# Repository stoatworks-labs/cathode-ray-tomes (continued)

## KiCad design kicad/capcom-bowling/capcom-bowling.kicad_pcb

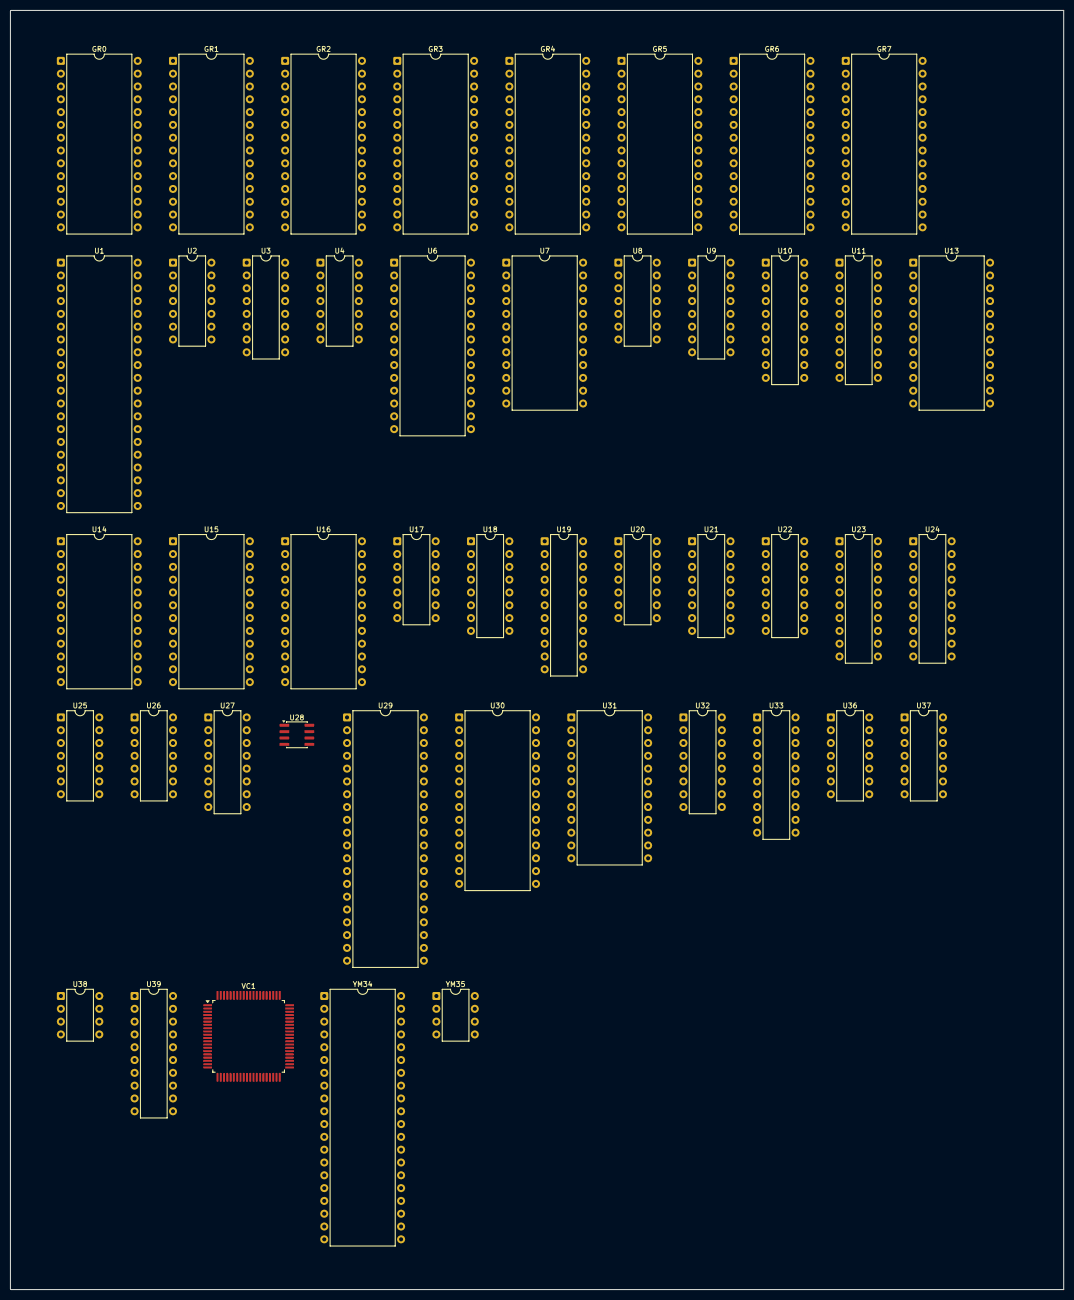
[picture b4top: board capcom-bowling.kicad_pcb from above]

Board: 2 copper layers, 208.9 x 253.7 mm, 46 parts (0 on the bottom side), 174 nets, no tracks yet.

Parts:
GR0, GR1, GR2, GR3, GR4, GR5, GR6, GR7: 27C256; DIP-28_W15.24mm
U1, U29: MC68B09E; DIP-40_W15.24mm
U2, U25: 74LS74; DIP-14_W7.62mm
U3: 74LS76; DIP-16_W7.62mm
U4: 74LS10; DIP-14_W7.62mm
U6, U30: 27C256; DIP-28_W15.24mm
U7, U31: HM6116P-3; DIP-24_W15.24mm
U8: 74LS04; DIP-14_W7.62mm
U9, U18, U32: 74LS138; DIP-16_W7.62mm
U10, U11, U33: 74HCT374; DIP-20_W7.62mm
U13, U14, U15, U16: TMS4461-15NL; DIP-24_W15.24mm
U17: 74LS14; DIP-14_W7.62mm
U19: TMS34070NL; DIP-22_W7.62mm
U20: 74LS86; DIP-14_W7.62mm
U21, U22, U27: 74LS191; DIP-16_W7.62mm
U23, U24: 74LS244; DIP-20_W7.62mm
U26: 74LS32; DIP-14_W7.62mm
U28: NE555; SOIC-8_3.9x4.9mm_P1.27mm
U36, U37: MC3403N; DIP-14_W7.62mm
U38: MB3730; DIP-8_W7.62mm
U39: DAC0832LCN; DIP-20_W7.62mm
VC1: TMS34061FNL; PQFP-80_14x14mm_P0.65mm
YM34: YM2203; DIP-40_W15.24mm
YM35: YM3014; DIP-8_W7.62mm

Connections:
/1P_START: U17.5, U24.15
/ PAL_MODE: U4.10, U4.11, U11.19
/-5V: U37.11, U39.8
/A0: GR0.10, GR1.10, GR2.10, GR3.10, GR4.10, GR5.10, GR6.10, GR7.10, U1.8, U6.10, U7.8, VC1.54
/A1: GR0.9, GR1.9, GR2.9, GR3.9, GR4.9, GR5.9, GR6.9, GR7.9, U1.9, U6.9, U7.7, U8.5
/A2: GR0.8, GR1.8, GR2.8, GR3.8, GR4.8, GR5.8, GR6.8, GR7.8, U1.10, U6.8, U7.6, VC1.51
/A3: GR0.7, GR1.7, GR2.7, GR3.7, GR4.7, GR5.7, GR6.7, GR7.7, U1.11, U6.7, U7.5, VC1.50
/A4: GR0.6, GR1.6, GR2.6, GR3.6, GR4.6, GR5.6, GR6.6, GR7.6, U1.12, U6.6, U7.4, VC1.49
/A5: GR0.5, GR1.5, GR2.5, GR3.5, GR4.5, GR5.5, GR6.5, GR7.5, U1.13, U6.5, U7.3, VC1.48
/A6: GR0.4, GR1.4, GR2.4, GR3.4, GR4.4, GR5.4, GR6.4, GR7.4, U1.14, U6.4, U7.2, VC1.47
/A7: GR0.3, GR1.3, GR2.3, GR3.3, GR4.3, GR5.3, GR6.3, GR7.3, U1.15, U6.3, U7.1, VC1.46
/A8: GR0.25, GR1.25, GR2.25, GR3.25, GR4.25, GR5.25, GR6.25, GR7.25, U1.16, U6.25, U7.23, U26.13, VC1.32
/A9: GR0.24, GR1.24, GR2.24, GR3.24, GR4.24, GR5.24, GR6.24, GR7.24, U1.17, U6.24, U7.22, U26.12, VC1.33
/A10: GR0.21, GR1.21, GR2.21, GR3.21, GR4.21, GR5.21, GR6.21, GR7.21, U1.18, U6.21, U7.19
/A11: GR0.23, GR1.23, GR2.23, GR3.23, GR4.23, GR5.23, GR6.23, GR7.23, U1.19, U6.23, U9.1
/A12: GR0.2, GR1.2, GR2.2, GR3.2, GR4.2, GR5.2, GR6.2, GR7.2, U1.20, U6.2
/A13: GR0.26, GR1.26, GR2.26, GR3.26, GR4.26, GR5.26, GR6.26, GR7.26, U1.21, U6.26, U9.2
/A14: U1.22, U6.27, U9.6, U18.5
/A15: U1.23, U9.4, U17.1, U18.4
/CLK_4M: U4.4, U19.14, U26.4, VC1.24, YM34.38
/CLK_8M: U2.3, U3.1, U3.6, U19.15, VC1.30
/COIN_2: U21.1, U21.15, U23.17
/D0: GR0.11, GR1.11, GR2.11, GR3.11, GR4.11, GR5.11, GR6.11, GR7.11, U1.31, U6.11, U7.9, U10.3, U11.3, U13.5, U16.5, U23.18, U24.18, U33.3, VC1.36
/D1: GR0.12, GR1.12, GR2.12, GR3.12, GR4.12, GR5.12, GR6.12, GR7.12, U1.30, U6.12, U7.10, U10.4, U11.4, U13.6, U16.6, U23.16, U24.16, U33.4, VC1.37
/D2: GR0.13, GR1.13, GR2.13, GR3.13, GR4.13, GR5.13, GR6.13, GR7.13, U1.29, U6.13, U7.11, U10.7, U11.7, U13.19, U16.19, U23.14, U24.14, U33.7, VC1.38
/D3: GR0.15, GR1.15, GR2.15, GR3.15, GR4.15, GR5.15, GR6.15, GR7.15, U1.28, U6.15, U7.13, U10.8, U11.8, U13.20, U16.20, U23.12, U24.12, U33.8, VC1.39
/D4: GR0.16, GR1.16, GR2.16, GR3.16, GR4.16, GR5.16, GR6.16, GR7.16, U1.27, U6.16, U7.14, U10.13, U11.13, U14.5, U15.5, U23.9, U24.9, U33.13, VC1.40
/D5: GR0.17, GR1.17, GR2.17, GR3.17, GR4.17, GR5.17, GR6.17, GR7.17, U1.26, U6.17, U7.15, U10.14, U11.14, U14.6, U15.6, U23.7, U24.7, U33.14, VC1.41
/D6: GR0.18, GR1.18, GR2.18, GR3.18, GR4.18, GR5.18, GR6.18, GR7.18, U1.25, U6.18, U7.16, U10.17, U11.17, U14.19, U15.19, U23.5, U24.5, U33.17, VC1.42
/D7: GR0.19, GR1.19, GR2.19, GR3.19, GR4.19, GR5.19, GR6.19, GR7.19, U1.24, U6.19, U7.17, U10.18, U11.18, U14.20, U15.20, U23.3, U24.3, U33.18, VC1.43
/E: U1.34, U3.11, U3.16, U4.2, U26.10, U29.34
/Q: U1.35, U3.9, U3.15, U26.9, U29.35
/RDY_~HOLD: U2.2, U4.12
/ROWA_LATCH: U9.15, U10.11
/R~W: U1.32, VC1.55
/SND_LATCH: U2.11, U9.11, U33.11
/main/ ~IN0: U9.9, U23.1, U23.19
/main/ROM_A14: GR0.27, GR1.27, GR2.27, GR3.27, GR4.27, GR5.27, GR6.27, GR7.27, U9.3, U11.2
/main/~BANK_CS: U9.14, U11.11
/main/~CEA: GR0.20, U18.15
/main/~CEB: GR1.20, U18.14
/main/~CEC: GR2.20, U18.13
/main/~CED: GR3.20, U18.12
/main/~CEE: GR4.20, U18.11
/main/~CEF: GR5.20, U18.10
/main/~CEG: GR6.20, U18.9
/main/~CEH: GR7.20, U18.7
/main/~CEI: U6.20, U17.2
/main/~E: U3.4, U3.10, U9.5
/main/~GROM_CS: U7.18, U9.13
/main/~IN1: U9.7, U24.1, U24.19
/main/~PL: U9.10, U21.11, U22.11, U27.11
/sound/IOUT1: U36.13, U39.11
/sound/LATCH_RD: U2.13, U32.7, U33.1
/sound/RFB: U36.14, U39.9
/sound/R~W: U8.11, U29.32, U31.21, YM34.35
/sound/SNDA0: U29.8, U30.10, U31.8, YM34.37
/sound/SNDA1: U29.9, U30.9, U31.7
/sound/SNDA2: U29.10, U30.8, U31.6
/sound/SNDA3: U29.11, U30.7, U31.5
/sound/SNDA4: U29.12, U30.6, U31.4
/sound/SNDA5: U29.13, U30.5, U31.3
/sound/SNDA6: U29.14, U30.4, U31.2
/sound/SNDA7: U29.15, U30.3, U31.1
/sound/SNDA8: U29.16, U30.25, U31.23
/sound/SNDA9: U29.17, U30.24, U31.22
/sound/SNDA10: U29.18, U30.21, U31.19
/sound/SNDA11: U29.19, U30.23
/sound/SNDA12: U29.20, U30.2, U32.1
/sound/SNDA13: U29.21, U30.26, U32.2
/sound/SNDA14: U29.22, U30.27, U32.3
/sound/SNDA15: U8.9, U29.23, U32.4
/sound/SND_D0: U29.31, U30.11, U31.9, U33.2, U39.7, YM34.8
/sound/SND_D1: U29.30, U30.12, U31.10, U33.5, U39.6, YM34.7
/sound/SND_D2: U29.29, U30.13, U31.11, U33.6, U39.5, YM34.6
/sound/SND_D3: U29.28, U30.15, U31.13, U33.9, U39.4, YM34.5
/sound/SND_D4: U29.27, U30.16, U31.14, U33.12, U39.16, YM34.4
/sound/SND_D5: U29.26, U30.17, U31.15, U33.15, U39.15, YM34.3
/sound/SND_D6: U29.25, U30.18, U31.16, U33.16, U39.14, YM34.2
/sound/SND_D7: U29.24, U30.19, U31.17, U33.19, U39.13, YM34.40
/sound/SND_~FIRQ: U29.4, YM34.25
/sound/~FM_CS: U32.14, YM34.34
/sound/~IRQ: U2.8, U29.3
/sound/~PCM_WR: U32.9, U39.2
/sound/~RAM_CS: U31.18, U32.15
/sound/~RD: U8.10, YM34.36
/sound/~ROM_CS: U8.8, U30.20
/video/MA0: U13.17, U14.17, U15.17, U16.17, VC1.6
/video/MA1: U13.16, U14.16, U15.16, U16.16, VC1.5
/video/MA2: U13.15, U14.15, U15.15, U16.15, VC1.4
/video/MA3: U13.14, U14.14, U15.14, U16.14, VC1.3
/video/MA4: U13.11, U14.11, U15.11, U16.11, VC1.2
/video/MA5: U13.10, U14.10, U15.10, U16.10, VC1.68
/video/MA6: U13.9, U14.9, U15.9, U16.9, VC1.67
/video/MA7: U13.13, U14.13, U15.13, U16.13, VC1.66
/video/RA0: U10.2, VC1.9
/video/RA1: U10.5, VC1.8
/video/RA2: U10.6, VC1.7
/video/RA3: U10.9, VC1.64
/video/RA4: U10.12, VC1.63
/video/RA5: U10.15, VC1.62
/video/RA6: U10.16, VC1.61
/video/RA7: U10.19, VC1.60
/video/SC: U4.6, U13.1, U14.1, U15.1, U16.1
/video/SDQ_A1: U13.2, U15.2, U19.5
/video/SDQ_A2: U13.3, U15.3, U19.6
/video/SDQ_A3: U13.22, U15.22, U19.7
/video/SDQ_A4: U13.23, U15.23, U19.8
/video/SDQ_B1: U14.2, U16.2, U19.19
/video/SDQ_B2: U14.3, U16.3, U19.18
/video/SDQ_B3: U14.22, U16.22, U19.17
/video/SDQ_B4: U14.23, U16.23, U19.16
/video/~CASLO: U13.18, U14.18, U15.18, U16.18, U26.1, VC1.20
/video/~HSYNC: U20.2, VC1.23
/video/~RAS0: U15.8, U16.8, VC1.17
/video/~RAS1: U13.8, U14.8, VC1.16
/video/~TR_~OE: U13.4, U14.4, U15.4, U16.4, VC1.57
/video/~VSYNC: U4.9, U20.1, VC1.22
/video/~WE: U13.7, U14.7, U15.7, U16.7, U26.3
/video/~W: U26.2, VC1.58
/~BLANK: U4.3, U19.12, VC1.21
/~MEM_OE: GR0.22, GR1.22, GR2.22, GR3.22, GR4.22, GR5.22, GR6.22, GR7.22, U6.22, U7.20, U8.2, U30.22, U31.20, U32.5
/~Q: U3.12, U3.14, U4.13
/~RESET: U1.37, U27.13, U29.37, VC1.56, YM34.24
/~VIDEOB_CS: U8.4, U13.21, U14.21
/~VIDEO_CE: U9.12, VC1.28, VC1.31
/~VIDEO_CS: U8.3, U11.16, U15.21, U16.21
/~VINT: U1.4, VC1.25
GNDPWR: GR0.14, GR1.14, GR2.14, GR3.14, GR4.14, GR5.14, GR6.14, GR7.14, U1.1, U1.39, U2.7, U3.13, U4.7, U6.14, U7.12, U8.7, U10.1, U10.10, U11.1, U11.10, U13.24, U14.24, U15.24, U16.24, U17.7, U19.3, U19.9, U19.11, U19.20, U20.7, U21.4, U21.8, U21.9, U21.10, U22.4, U22.8, U22.9, U22.15, U23.10, U24.10, U25.7, U26.7, U27.4, U27.5, U27.8, U27.9, U27.15, U28.1, U29.1, U29.39, U30.14, U31.12, U33.10, U36.5, U36.10, U36.12, U38.4, U39.1, U39.10, U39.12, U39.17, VC1.1, VC1.11, VC1.13, VC1.27, VC1.34, VC1.52, YM34.1, YM35.6
unnamed: U2.5, U3.3, U3.7
unnamed: U11.6, U18.1
unnamed: U11.9, U18.2
unnamed: U11.12, U18.3
unnamed: U4.1, U17.4
unnamed: U8.1, U18.6, U26.8
unnamed: U19.10, U20.11
unnamed: U20.3, U20.5
unnamed: U20.9, U26.11
unnamed: U8.6, U20.10
unnamed: U4.8, U20.12
unnamed: U17.10, U21.14, U25.3
unnamed: U21.5, U25.6
unnamed: U21.3, U23.2
unnamed: U21.2, U23.4
unnamed: U21.6, U23.6
unnamed: U21.7, U23.8
unnamed: U17.12, U22.14, U25.11
unnamed: U22.5, U25.8
unnamed: U22.3, U24.2
unnamed: U22.2, U24.4
unnamed: U22.6, U24.6
unnamed: U22.7, U24.8
unnamed: U17.6, U25.2
unnamed: U17.8, U25.12
unnamed: U27.14, U28.3
unnamed: U28.2, U28.6
unnamed: U36.3, YM35.7
unnamed: U36.1, U36.2, YM35.8
unnamed: U36.6, U36.7
unnamed: U36.8, U36.9
unnamed: U37.3, YM34.18
unnamed: U37.1, U37.2
unnamed: U37.5, YM34.19
unnamed: U37.6, U37.7
unnamed: U37.10, YM34.20
unnamed: U37.8, U37.9
unnamed: U37.12, YM35.2
unnamed: U37.13, U37.14
unnamed: U20.8, VC1.53
unnamed: U17.3, VC1.26
unnamed: YM34.23, YM35.4
unnamed: YM34.39, YM35.5
unnamed: YM34.22, YM35.3
VCC: GR0.1, GR0.28, GR1.1, GR1.28, GR2.1, GR2.28, GR3.1, GR3.28, GR4.1, GR4.28, GR5.1, GR5.28, GR6.1, GR6.28, GR7.1, GR7.28, U1.3, U1.7, U1.40, U2.1, U2.4, U2.10, U2.12, U2.14, U3.2, U3.5, U3.8, U4.14, U6.1, U6.28, U7.24, U8.14, U10.20, U11.20, U13.12, U14.12, U15.12, U16.12, U17.14, U19.2, U19.13, U20.4, U20.13, U20.14, U21.16, U22.16, U23.20, U24.20, U25.1, U25.4, U25.10, U25.13, U25.14, U26.14, U27.16, U28.4, U28.8, U29.2, U29.7, U29.40, U30.1, U30.28, U31.24, U32.6, U33.20, U38.7, U39.19, U39.20, VC1.10, VC1.29, VC1.44, VC1.45, VC1.59, YM34.21, YM35.1

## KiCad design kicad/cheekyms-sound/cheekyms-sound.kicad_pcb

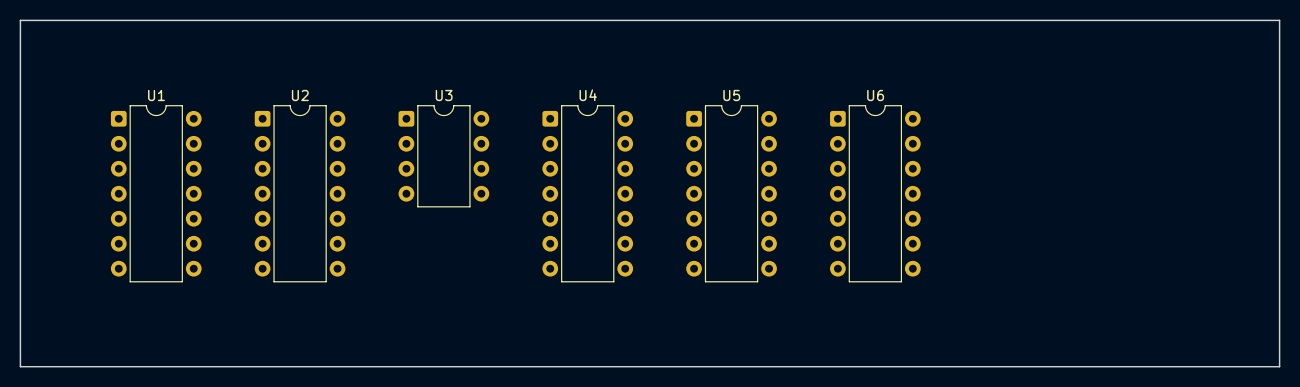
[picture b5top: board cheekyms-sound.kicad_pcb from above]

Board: 2 copper layers, 128.0 x 35.2 mm, 6 parts (0 on the bottom side), 9 nets, no tracks yet.

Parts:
U1: 7404; DIP-14_W7.62mm
U2, U4, U6: NE556; DIP-14_W7.62mm
U3: NE555; DIP-8_W7.62mm
U5: LM324; DIP-14_W7.62mm

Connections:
+5V: U1.14, U2.14, U3.4, U3.8, U4.14, U5.4, U6.4, U6.10, U6.14
GND: U1.7, U2.7, U3.1, U4.7, U5.11, U6.7
unnamed: U4.2, U4.6
unnamed: U6.2, U6.6
unnamed: U3.2, U3.6
unnamed: U6.8, U6.12
unnamed: U2.8, U2.12
unnamed: U2.2, U2.6
unnamed: U4.8, U4.12

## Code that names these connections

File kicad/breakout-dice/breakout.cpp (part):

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#endif

   //HSYNC and VSYNC
   #define H1_d 		"L1", 14
   #define H2_d 		"L1", 13
   #define H4_d 		"L1", 12
   #define H8_d 		"L1", 11
   #define H8_n 	"J2", 2
   #define H16_d  	"K1", 14
   #define H16_n 	"J2", 6
   #define H32_d 	 	"K1", 13
   #define H32_n 	"J2", 4
   #define H64_d 	 	"K1", 12
   #define H128_d  	"K1", 11

   #define V1_d 	 	"M1", 14
   #define V2_d 	 	"M1", 13
   #define V4_d 	 	"M1", 12
   #define V8_d 	 	"M1", 11
   #define V16_d 	 	"N1", 14
   #define V16_n 	"J2", 10
   #define V32_d 	 	"N1", 13
   #define V64_d 	 	"N1", 12
   #define V64I  	"H7", 11
   #define V64_n 	"M9", 10
   #define V128_d  	"N1", 11

   #define H1		"L2", 8
   #define H2		"L2", 11
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   #define V64		"N3", 6
   #define V128		"N3", 11

   #define HSYNC  	"J1", 2
   #define HSYNC_n  	"J1", 3
   #define VSYNC  	"J1", 7
   #define VSYNC_n  	"J1", 6
   #define PSYNC  	"J1", 11
   #define PSYNC_n  	"J1", 10
   #define BSYNC  	"J1", 15
   #define BSYNC_n  	"J1", 14

   #define BALL 	"D7", 6 
   #define BALL_DISPLAY "A4", 6
   #define PLAYFIELD 	"H4", 3 
   #define SCORE 	"D3", 5  
   #define VERT_TRIG_n 	"H1", 8

   #define CLOCK 	"H1", 11
   #define SCLOCK 	"K1", 15
   #define CKBH 	"F1", 13

   #define PAD_n 	"K3", 8
   #define PAD_EN_n 	"C2", 8

   #define P VCC

   #define COIN 		"L9", 6
   #define COIN1_n 		"F8", 5
   #define COIN2_n 		"H9", 5   
   #define CREDIT_1_OR_2 	"L9", 3
   #define CREDIT_1_OR_2_n 	"F9", 8
   #define CREDIT2 		"F9", 6
   #define CREDIT2_n 		"M8", 8
   #define CR_START1 		"E8", 5
   #define CR_START1_n 		"E8", 6	//Schematic shows E8.6 as positive CR_START1, but this can't be right?
   #define CR_START2 		"E8", 9
   #define CR_START2_n 		"E8", 8
   #define CSW1 		"F9", 12
   #define CSW2 		"F9", 2

   #define P2_CONDITIONAL	"H1", 3
   #define P2_CONDITIONAL_dash 	"H7", 8
   #define PLAYER_2 		"B4", 14 
   #define PLAYER_2_n 		"M9", 8

   #define START_GAME 		"D8", 6
   #define START_GAME1_n 	"M9", 4
   #define START_GAME_n 	"M9", 6

   #define BG1_n	"K8", 9
   #define BG1 		"K8", 8
   #define BG2_n	"K8", 5
   #define BG2		"K8", 6
 
   #define FREE_GAME_TONE	"N7", 3
   #define BONUS_COIN		"L9", 11
 
   #define Q 		"E9", 6
   #define Q_n 		"LATCH", 3
   #define SBD_n 	"D2", 11

   #define PLAY_CP 	"D2", 8
   #define PLGM2_n 	"F7", 7	
   #define VB_HIT_n 	"A5", 6

   #define SERVE_n 	"SERVE", 1
   #define SERVE_WAIT 	"A3", 9
   #define SERVE_WAIT_n "A3", 8   

   #define BRICK_DISPLAY 	"E3", 1   
   #define BRICK_HIT 		"E6", 5
   #define BRICK_HIT_n 		"E6", 6

   //#define EGL 		"A4", 3
   #define EGL		"C37" , 2
   #define EGL_n 	"C5", 2

   #define RAM_PLAYER1 	"E7", 4
   #define A1 		"H6", 14
   #define B1 		"H6", 13
   #define C1 		"H6", 12
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   #define DN 		"C4", 3
   #define PC 		"D4", 12
   #define PD 		"D4", 11
   #define SU_n 	"D5", 8
   #define V_SLOW 	"C5", 8

   #define PLNR 	"E3", 4
   #define SCI_n 	"H4", 6
   #define SFL_n 	"E9", 12	//score flash
   #define TOP_n 	"E9", 2

   #define BP_HIT_n 	"A5", 8
   #define BTB_HIT_n 	"C3", 3

   #define SET_BRICKS 	"D3", 9
   #define SET_BRICKS_n "D3", 8

   #define BALL_A 	"B4", 13
   #define BALL_B 	"B4", 12
   #define BALL_C 	"B4", 11

   #define FPD1 	"F3", 10
   #define FPD1_n 	"F3", 9
   #define FPD2 	"F3", 6
   #define FPD2_n 	"F3", 7
 
   #define COUNT 	"N7", 11
   #define COUNT_1 	"N7", 8
   #define COUNT_2 	"N7", 6

   #define ATTRACT 	"E6", 8
   #define ATTRACT_n 	"E6", 9
   
   #define BRICK_SOUND 	"B8", 14
   #define P_HIT_SOUND 	"B7", 12
   #define VB_HIT_SOUND "B7", 11

   #define LH_SIDE 	"J3", 13
   #define RH_SIDE 	"H2", 3
   #define TOP_BOUND 	"K4", 6
   
//   CONNECTION(CREDIT_1_OR_2, "CREDIT_LIGHT1", 1)
//   CONNECTION(CREDIT2, "CREDIT_LIGHT2", 1)
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   CONNECTION("VIDEO", 5, "B9", 3)
   //CONNECTION("VIDEO", 6, P)

   CONNECTION("VIDEO", Video::HBLANK_PIN, HSYNC)
   CONNECTION("VIDEO", Video::VBLANK_PIN, "E3", 10)
   

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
